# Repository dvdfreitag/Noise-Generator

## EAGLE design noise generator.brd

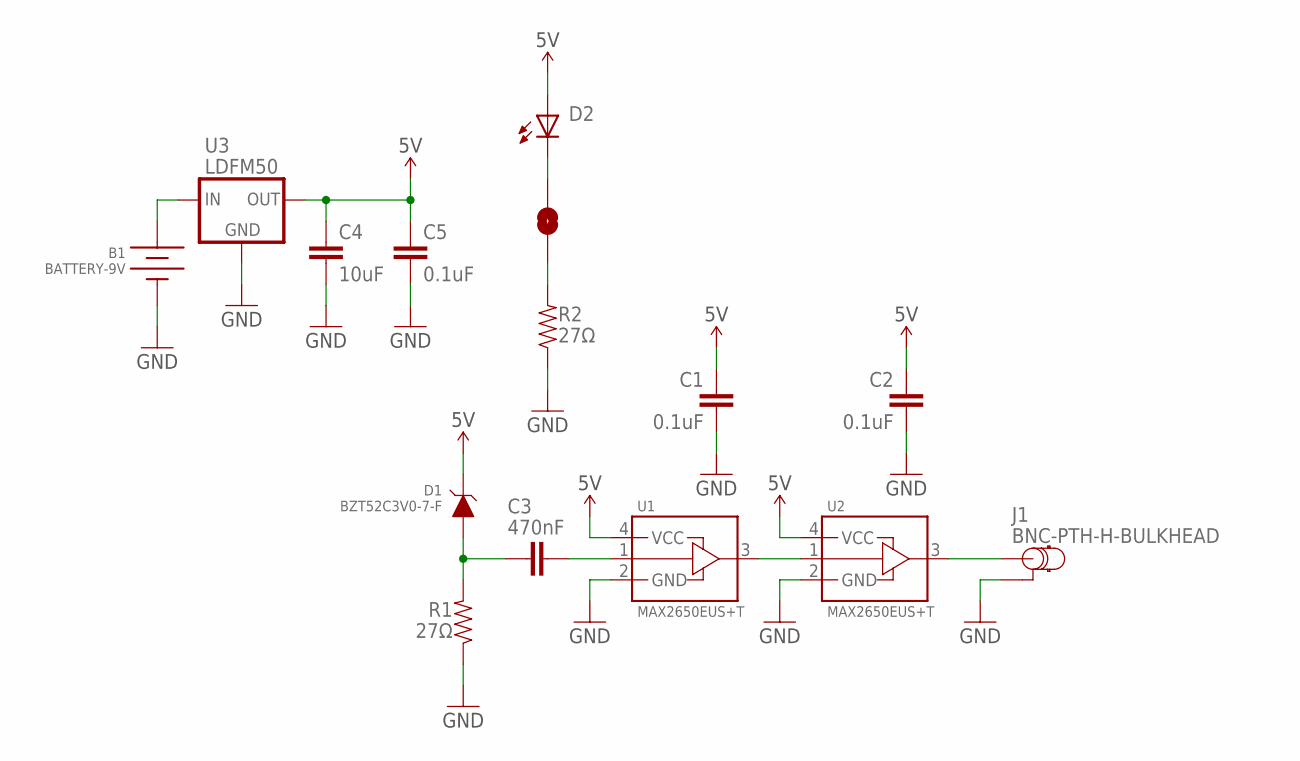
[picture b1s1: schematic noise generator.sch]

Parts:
B1: BATTERY-9V; 9V-NEG
C1, C2, C5: 0.1uF; 1206
C3: 470nF; 1206
C4: 10uF; 1206
D1: BZT52C3V0-7-F; SOD123
D2: LED-0805; 0805-LED
J1: BNC-PTH-H-BULKHEAD; BNC-5-1634556-0
R1, R2: 27Ω; 1206
SJ1: SOLDERJUMPERNO; SJ_2S-NO
U1, U2: MAX2650EUS+T; SOT-143-4
U3: LDFM50; DPAK

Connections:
5V: C1.1, C2.1, C4.1, C5.1, D1.CATHODE (C), D2.A, U1.4 (VCC), U2.4 (VCC), U3.3 (OUT)
GND: B1.N1 (N), B1.N2 (N), B1.N3 (N), C1.2, C2.2, C4.2, C5.2, J1.P$1 (GND), J1.P$2 (GND), J1.P$3 (GND), J1.P$4 (GND), R1.1, R2.1, U1.2 (GND), U2.2 (GND), U3.TAB (GND)
unnamed: C3.1, D1.ANODE (A), R1.2
unnamed: U1.3 (OUT), U2.1 (IN)
unnamed: C3.2, U1.1 (IN)
unnamed: J1.1 (SIGNAL), U2.3 (OUT)
unnamed: R2.2, SJ1.1
unnamed: B1.P1, B1.P2, B1.P3, U3.1 (IN)
unnamed: D2.C, SJ1.2

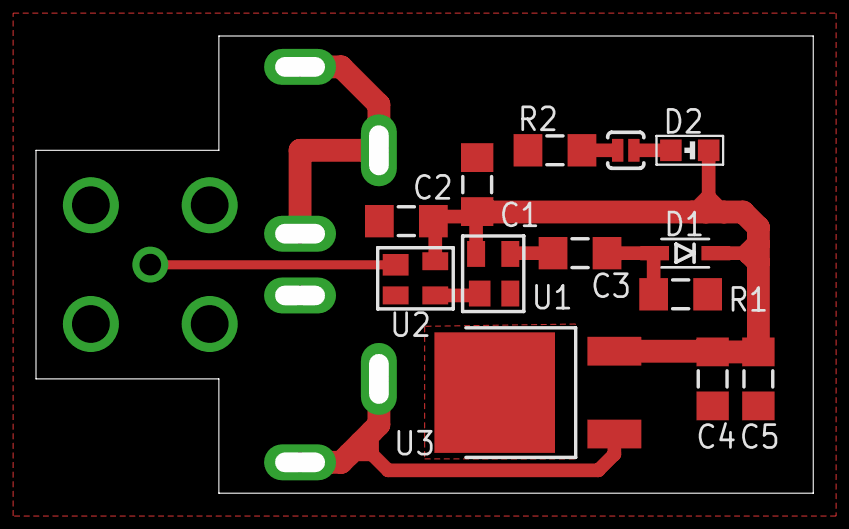
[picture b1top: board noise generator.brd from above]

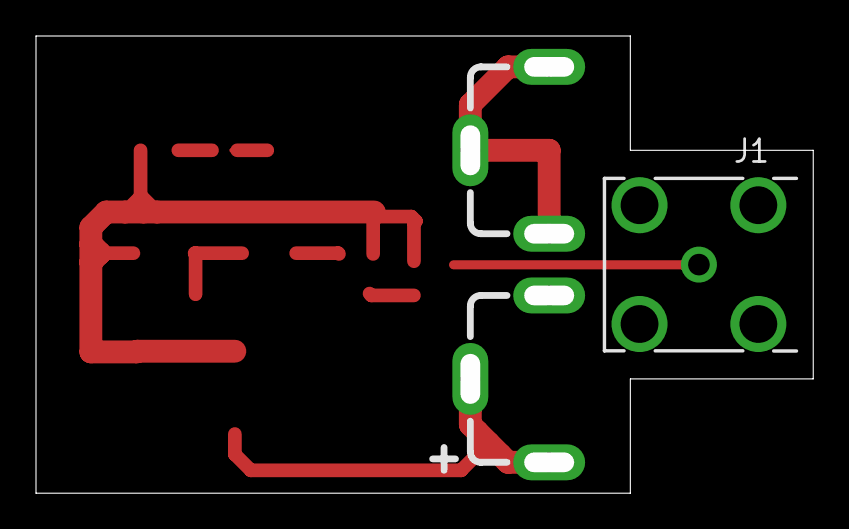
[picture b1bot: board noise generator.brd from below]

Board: 2 copper layers, 42.1 x 24.3 mm, 15 parts (2 on the bottom side), 9 nets.

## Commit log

2016-08-12 Create LICENSE
2016-08-12 Added documents
2016-08-12 Added pdf drawings

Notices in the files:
parts and their libraries:
SparkFun-Passives: Licensing: CC v3.0 Share-Alike You are welcome to use this library for commercial purposes.
